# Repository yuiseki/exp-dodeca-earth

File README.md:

# exp-dodeca-earth

正十二面体の地球儀。12 の面それぞれに 1.28 インチの丸型 LCD (Waveshare 1.28inch LCD Module、GC9A01) を置き、その面から見た地球を映す。正十二面体は、面 6 枚ずつの同じお椀 2 個に分けて 3D プリントし、磁石で合わせる。お椀 1 個ぶんの LCD 6 枚を、XIAO ESP32-S3 1 枚と 74HC138 で駆動する。

## 中身

- `3d/pentagon/`: お椀と面の板の形 (版ごと)。`build.py` が STEP と STL を書く。いまの版は `v0.0.5` (同じお椀を 2 個印刷する)
- `simulate/`: 板と LCD を組み上げたときの当たり、磁石の極、ケーブルの取り回しを確かめるスクリプト
- `hardware/hub6_one/`: お椀 1 個ぶんの LCD 6 枚を駆動する基板 (1 枚、2 層)。`fab6/` が JLCPCB に出したファイル
- `hardware/hub6/`: 同じ役目の基板の、使わなかった案
- `firmware/hub6_bench/`: ブレッドボードで 6 枚を駆動するスケッチと、地球の画像を面ごとに切り出すスクリプト

## LCD モジュールの 3D 図面

`simulate/` のスクリプトは、Waveshare が配っている LCD モジュールの 3D 図面を読む。再配布の条件が書かれていないので、このリポジトリには入れていない。[Waveshare の wiki](https://www.waveshare.com/wiki/1.28inch_LCD_Module) の 3D Drawing (`1.28inch_LCD_Module_3D_Drawing.zip`) を取ってきて、`3d/display/` に展開する:

```sh
mkdir -p 3d/display && cd 3d/display
curl -LO https://files.waveshare.com/upload/4/49/1.28inch_LCD_Module_3D_Drawing.zip
unzip 1.28inch_LCD_Module_3D_Drawing.zip -d 1.28inch_LCD_Module_3D_Drawing
```

`3d/display/1.28inch_LCD_Module_3D_Drawing/1.28inch LCD Module 3D Drawing/0508.stp` ができればよい。LCD を含むメッシュ (`simulate/*/overlay.stl`、`overlay.3mf`、`dodecahedron*.3mf`) も同じ理由で入れていない。スクリプトを動かすと作られる。

## ライセンス

MIT (`LICENSE`)。

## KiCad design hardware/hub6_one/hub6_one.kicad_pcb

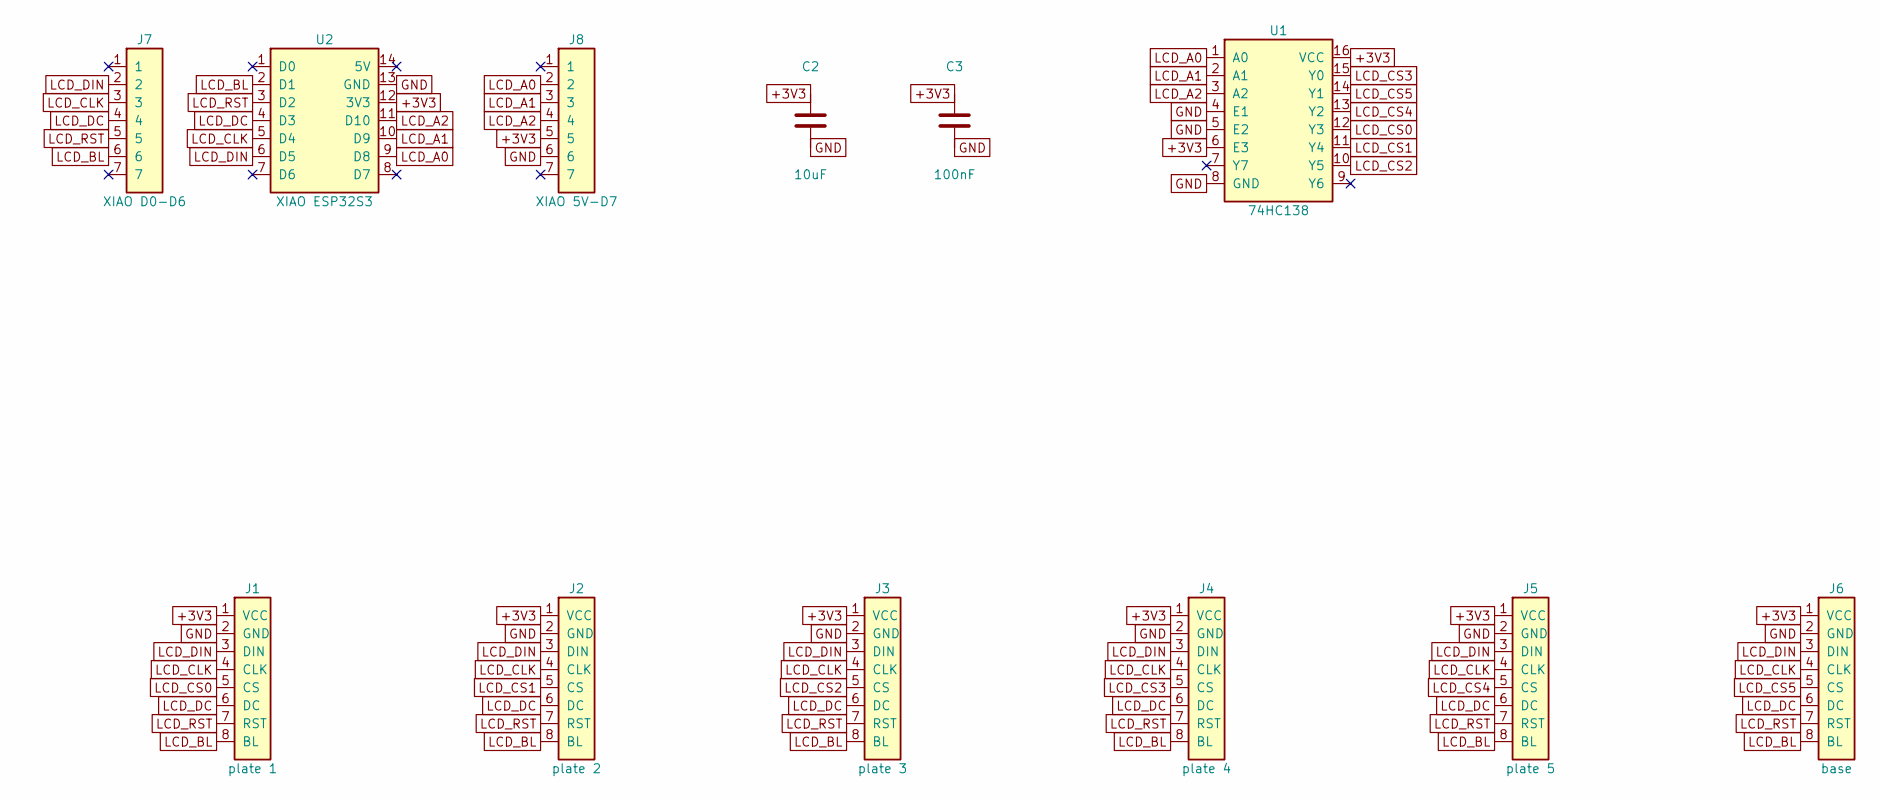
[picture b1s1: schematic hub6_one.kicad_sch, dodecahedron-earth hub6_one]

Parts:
C2: 10uF; C_0805_2012Metric; LCSC C15850
C3: 100nF; C_0603_1608Metric; LCSC C14663
J1: plate 1; Wire_1x08_P2.80
J2: plate 2; Wire_1x08_P2.80
J3: plate 3; Wire_1x08_P2.80
J4: plate 4; Wire_1x08_P2.80
J5: plate 5; Wire_1x08_P2.80
J6: base; Wire_2x04_P2.54
J7: XIAO D0-D6; PinSocket_1x07_P2.54mm_Vertical; LCSC C27985232
J8: XIAO 5V-D7; PinSocket_1x07_P2.54mm_Vertical; LCSC C27985232
U1: 74HC138; SOIC-16_3.9x9.9mm_P1.27mm; LCSC C2674688
U2: XIAO ESP32S3

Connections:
+3V3: C2.1, C3.1, J1.1 (VCC), J2.1 (VCC), J3.1 (VCC), J4.1 (VCC), J5.1 (VCC), J6.1 (VCC), J8.5, U1.6 (E3), U1.16 (VCC), U2.12 (3V3)
GND: C2.2, C3.2, J1.2 (GND), J2.2 (GND), J3.2 (GND), J4.2 (GND), J5.2 (GND), J6.2 (GND), J8.6, U1.4 (E1), U1.5 (E2), U1.8 (GND), U2.13 (GND)
LCD_A0: J8.2, U1.1 (A0), U2.9 (D8)
LCD_A1: J8.3, U1.2 (A1), U2.10 (D9)
LCD_A2: J8.4, U1.3 (A2), U2.11 (D10)
LCD_BL: J1.8 (BL), J2.8 (BL), J3.8 (BL), J4.8 (BL), J5.8 (BL), J6.8 (BL), J7.6, U2.2 (D1)
LCD_CLK: J1.4 (CLK), J2.4 (CLK), J3.4 (CLK), J4.4 (CLK), J5.4 (CLK), J6.4 (CLK), J7.3, U2.5 (D4)
LCD_CS0: J1.5 (CS), U1.12 (Y3)
LCD_CS1: J2.5 (CS), U1.11 (Y4)
LCD_CS2: J3.5 (CS), U1.10 (Y5)
LCD_CS3: J4.5 (CS), U1.15 (Y0)
LCD_CS4: J5.5 (CS), U1.13 (Y2)
LCD_CS5: J6.5 (CS), U1.14 (Y1)
LCD_DC: J1.6 (DC), J2.6 (DC), J3.6 (DC), J4.6 (DC), J5.6 (DC), J6.6 (DC), J7.4, U2.4 (D3)
LCD_DIN: J1.3 (DIN), J2.3 (DIN), J3.3 (DIN), J4.3 (DIN), J5.3 (DIN), J6.3 (DIN), J7.2, U2.6 (D5)
LCD_RST: J1.7 (RST), J2.7 (RST), J3.7 (RST), J4.7 (RST), J5.7 (RST), J6.7 (RST), J7.5, U2.3 (D2)

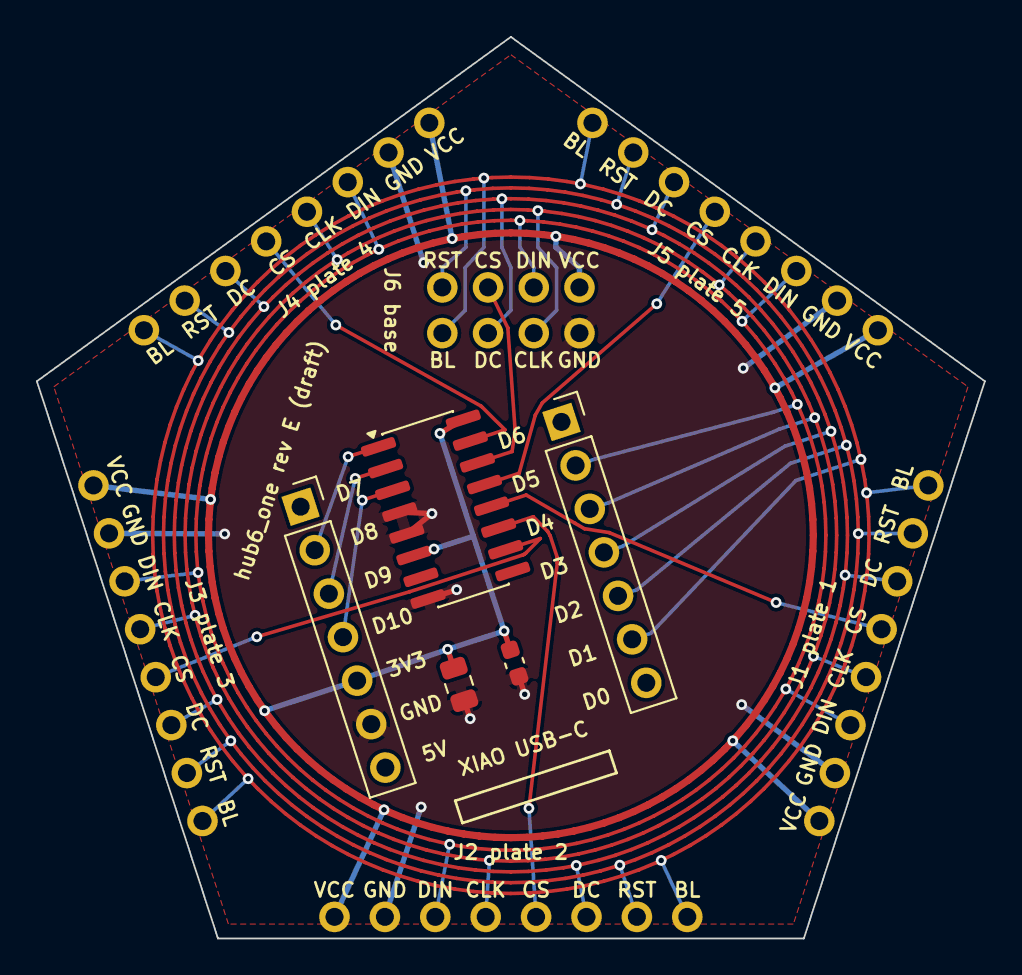
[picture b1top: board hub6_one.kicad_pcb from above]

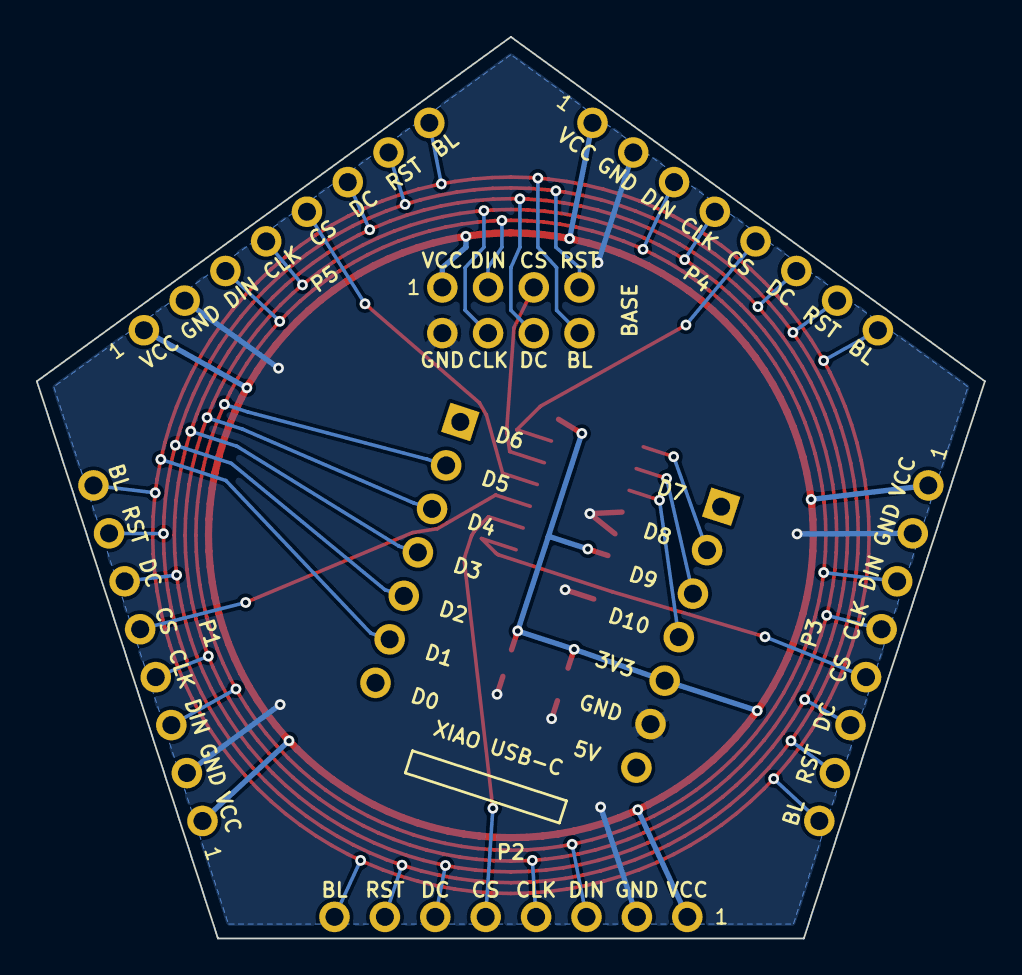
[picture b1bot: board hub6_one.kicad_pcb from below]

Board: 2 copper layers, 52.7 x 50.1 mm, 12 parts (7 on the bottom side), 16 nets.

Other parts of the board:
X1: XIAO; XIAO_ESP32S3_Hanging

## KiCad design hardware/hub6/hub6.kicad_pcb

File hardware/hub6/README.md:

# hub6

お椀 1 個ぶん、1.28 インチ丸型 LCD (Waveshare 1.28inch LCD Module、GC9A01、PH2.0 8 ピン) 6 枚を、XIAO ESP32-S3 1 枚と 74HC138 で駆動する基板。2 つのお椀に 1 枚ずつ載せる。

- 形: 辺までの距離 26 mm の正五角形。5 つの辺が、お椀の 5 枚の側面に 1 対 1 で向き合う。4 層、片面実装
- お椀の中の高さ: 基板の底面を、お椀の底の外面から 17〜20 mm に置くと、壁と当たらない (`3d/pentagon/v0.0.5/lcd_cup.stl` を輪切りにして測った。20 mm なら、壁との隙間 1 mm を取っても辺まで 27.4 mm まで入る)。固定の仕方は未定
- ケーブル: ディスプレイ側は PH2.0 のプラグ、基板側はより線 (26 AWG) のケーブル (Amazon B0GFCDKFH9、15 cm) を、現物合わせの長さに切って、基板の穴に直接はんだ付けする。ディスプレイ側は抜き差しできるので、基板を差し替えるときは、ケーブルごと取り替える
- J1〜J5: 側面のディスプレイ用の穴の列 (8 個、2.54 mm おき、穴 1.0 mm)。五角形の辺に沿って並び、ケーブルは上 (お椀の口の側) から来る。列の外側に、ケーブルを押さえる結束バンド (幅 2.5 mm) 用のスロットが 2 つずつある。ホットボンドで固めてもよい
- J6: 底面のディスプレイ用の穴の列。XIAO の右のソケット列のすぐ外側 (2.88 mm) にあり、底面のディスプレイのプラグのほぼ真上 (約 4 mm ずれ) にある。ケーブルは下から来るので、下から穴に通して、上面ではんだ付けする
- J7、J8: XIAO 用の 1x7、2.54 mm のメスのピンソケット (XFCN PM254V-11-07-H85、LCSC C2832270、高さ 8.5 mm)。XIAO は基板の中心に挿す (手で)。USB-C は方位 72 度を向く
- U1: 74HC138 (SOIC-16、LCSC C5602)。XIAO の下の、ソケットの 2 列の間に置く。A0、A1、A2 の 3 本から、6 枚の CS を作る。E1、E2 は GND、E3 は 3V3 に固定 (常に有効)
- C2: 10uF (LCSC C15850)、3.3V のバルク。C3: 100nF (LCSC C14663)、U1 の 3.3V。どちらも XIAO の下

## どの列がどのディスプレイか

お椀を底面で立てて、上から見て反時計回りに板 1〜5 (`simulate/v0.0.5/magnets.csv` と同じ番号)、そして底面。基板は、お椀の軸に中心を合わせ、方位 (上から見て反時計回り、お椀の座標と同じ) をそろえて置く。

| 列 | ディスプレイ | 基板上の方位 | CS のネット | U1 の出力 | アドレス (A2 A1 A0) |
|---|---|---|---|---|---|
| J1 | 板 1 | 198 度 | LCD_CS0 | Y0 (15 番) | 0 (000) |
| J2 | 板 2 | 270 度 | LCD_CS1 | Y1 (14 番) | 1 (001) |
| J3 | 板 3 | 342 度 | LCD_CS2 | Y2 (13 番) | 2 (010) |
| J4 | 板 4 | 54 度 | LCD_CS3 | Y3 (12 番) | 3 (011) |
| J5 | 板 5 | 126 度 | LCD_CS4 | Y5 (10 番) | 5 (101) |
| J6 | 底面 | XIAO の右 (162 度の側) | LCD_CS5 | Y4 (11 番) | 4 (100) |

アドレスの 6 と 7 (Y6、Y7) は使わない。ファームウェアでは、全部の CS を「選んでいない」状態にしたいときはアドレスを 7 にする (Y7 は何にもつながっていない)。

穴の番号は、ディスプレイの PH2.0 の番号と同じ: 1 VCC、2 GND、3 DIN、4 CLK、5 CS、6 DC、7 RST、8 BL (Waveshare の配線表の順。ピン番号の並びは、実機で確かめる)。ケーブルの線 n を、穴 n に入れる。1 番の穴は、シルクの「1」の側。側面の列 (J1〜J5) では、上から見て反時計回りの端。

共有の信号 (6 枚とも同じ) と、XIAO のピン:

| 信号 | XIAO のピン |
|---|---|
| LCD_DIN (SPI MOSI) | D0 |
| LCD_CLK (SPI SCK) | D1 |
| LCD_DC | D3 |
| LCD_RST | D4 |
| LCD_BL | D5 |
| A0、A1、A2 (74HC138 のアドレス) | D7、D8、D9 |
| つないでいない (予備) | D2、D6、D10 |

この並びは、J6 の穴 3、4、6、7、8 が、XIAO の D0、D1、D3、D4、D5 の真横に来るように決めた (D2 の横は J6 の 5 番、CS)。SPI は GPIO マトリクス経由なので、どのピンでも動く。D2 (GPIO3) はストラッピングピン、D6/D7 (GPIO43/44) は UART0。D2、D6、D10 の 3 本が空いているので、2 台の同期は、配線 (予備の 1 本) か、ESP-NOW などの無線のどちらでも取れる。

74HC138 は 3.3V で動かす (HC 系は 2V から 6V)。出力の「高」は電源に近い電圧なので、ディスプレイ側の TXB0108 のしきい値 (3.3V のとき 2.15V) を超える。出力が切り替わる瞬間に、短いひげ (グリッチ) が CS に出ることがあるが、SCK が止まっている間なので、ディスプレイは何も読み込まない。ただし、アドレスは SCK が止まっているとき (転送の合間) にだけ変えること。

## 電源は 3.3V

ディスプレイの VCC は XIAO の 3V3 に直結し、XIAO の 5V ピンは使わない。理由: ディスプレイは 5V→3.3V の電源 IC と、TXB0108 のレベル変換 IC を載せていて、その信号側の基準電圧は VCC。VCC を 5V にすると、信号の「高」の下限は 0.65 x 5V = 3.25V (TXB0108 のデータシート 5.3) で、XIAO の 3.3V の出力 (ESP32-S3 は下限 2.64V) では読み取りが保証されない。VCC = 3.3V なら下限は 2.15V。

6 枚で約 190 mA (74HC138 は数 uA で、足しても変わらない) (Waveshare の最大値、1 枚 31.2 mA)。XIAO の 3V3 ピンは 700 mA (Seeed の記載) まで取れる。USB 給電の間は、XIAO のレギュレーターが (5 - 3.3)V x 約 0.3A = 約 0.5W の熱を出す。実機で温度を測る。

## 層

| 層 | 中身 |
|---|---|
| F.Cu | 信号の短い線 (各列から輪への放射状の線、XIAO から J6 と U1 への線、U1 の出力から via への線、via から側面の列の 5 番までの線)、部品 |
| In1.Cu | GND の面 |
| In2.Cu | 共有の 5 信号の輪 (中心を囲む同心円。半径 17.6、18.4、19.2、20.0、20.8 mm。どの信号がどの輪かは `layout.json`)。輪の内側 (半径 17.1 mm まで) は、U1 の 6 本の出力の線 (CS) が、ソケットのピンの隙間を縫って走る |
| B.Cu | +3V3 の面 |

スルーホールのパッドは、GND と +3V3 の面に直接つながる。側面の列は内向きに、J6 は外向きに、放射状の線で輪につながる。XIAO は J6 を通して輪につながる。配線は自動配線ではなく、`assign.py` が探して `layout.json` に書いた線を `make.py` が引く (Freerouting は 2 層でも 4 層でも、共有バスと選択線の構造を見つけられずに止まった)。

## 作り方

```sh
/usr/bin/python3 make.py    # 回路図、部品と配線を置いた基板、ライブラリ (KiCad 10 の pcbnew モジュールを使う)
./check.sh                  # ERC、DRC (回路図との突き合わせ込み)、test_hub6.py。どれも 0 件で通る
/usr/bin/python3 fab.py     # JLCPCB 用: build/fab/ にガーバーとドリルの zip、BOM、部品配置 (CPL)。fab6/ に写す
../../.venv/bin/python assign.py   # 配線を探し直して layout.json を書く (shapely が要る。数秒)
```

- 部品と網の表は `make.py` の先頭にあり、回路図と基板の両方がそこから作られる
- `test_hub6.py` は `make.py` とは別に、設計表から各パッドの網と、列の位置と向き、XIAO と部品の位置、穴とスロットの大きさを確かめる
- `assign.py`: ① 共有 5 信号を、どの輪に載せるか (J6 と側面の列からの放射状の線が、互いにぶつからない順を探す。120 通りのうち 4 通りが通る)。② 74HC138 の出力 6 本を、どの列につなぎ、どこで In2 から F.Cu に上げ、In2 のどこを通すか (ソケットの隙間を通る最短経路を、見通しグラフで探す)。結果が `layout.json` で、`make.py` と `test_hub6.py` はこの結果を前提にする (テストの表は手で写してあるので、`layout.json` を変えたらテストも直す)

## JLCPCB での組み立て

- 経済的な実装 (Economic PCBA) は、4 層に対応し、片面 (上面) だけ。載せる部品はすべて上面
- 載せる部品は U1、C2、C3 (表面実装) と、J7、J8 (XIAO のソケット、スルーホールの手はんだ、Manual Assembly、1 か所 0.0164 ドル)。J1〜J6 は穴だけで、部品はない (BOM と CPL に出ない)
- U1 (C5602) は、JLCPCB の拡張部品 (Extended)。基本部品ではないので、部品の種類ごとに追加費用が 1 種類ぶんかかる。C2 (C15850) と C3 (C14663) は基本部品
- 五角形の外形と、側面の列のスロット (1.3 x 2.9 mm の長穴、メッキなし) は、見積もりの画面で通るか確かめる

## 発注の前に確かめること

- XIAO で 6 枚を実際に駆動して、画面の乱れ、更新の速さ (40MHz で 6 枚を順に送ると約 7fps)、XIAO のレギュレーターの温度を確かめる (実機でしか分からない)
- JLCPCB の部品配置の確認画面で、U1 と J7、J8 の向き。SOIC-16 とソケットの JLCPCB 上の向きは、cubic-earth の hub3 で確かめた補正 (`fab.py` の `JLC_ROTATION_OFFSET`) を使っているが、この基板では未確認
- 4 層の基板の費用
- ケーブルの 1 番の線の色。ディスプレイ側のヘッダーの 1 番 (VCC) が、ケーブルのどの色の線になるかを、テスターで確かめてから穴に入れる
- 底面のディスプレイのプラグの 1 番が、J6 の 1 番 (XIAO の USB-C の側) と同じ向きか。逆なら、線が 8 本とも J6 の上で交差する (動きはするが、はんだ付けの間違いが起きやすい)

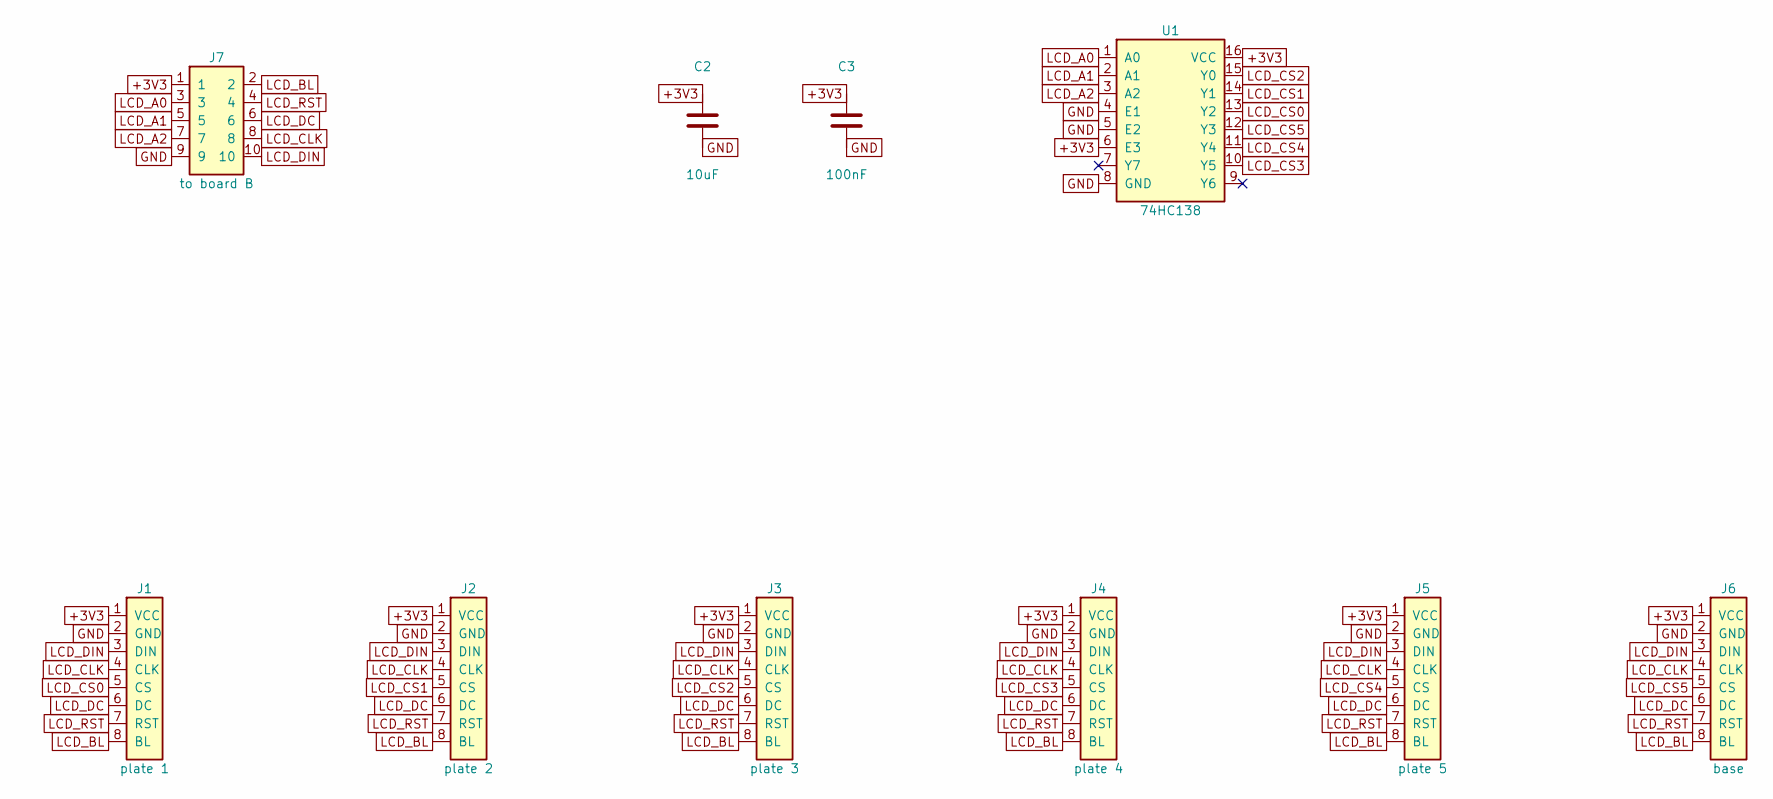
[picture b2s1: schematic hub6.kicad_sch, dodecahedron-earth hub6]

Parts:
C2: 10uF; C_0805_2012Metric; LCSC C15850
C3: 100nF; C_0603_1608Metric; LCSC C14663
J1: plate 1; Wire_1x08_P2.54_Tie
J2: plate 2; Wire_1x08_P2.54_Tie
J3: plate 3; Wire_1x08_P2.54_Tie
J4: plate 4; Wire_1x08_P2.54_Tie
J5: plate 5; Wire_1x08_P2.54_Tie
J6: base; Wire_2x04_P2.54
J7: to board B; PinHeader_2x05_P2.54mm_Vertical
U1: 74HC138; SOIC-16_3.9x9.9mm_P1.27mm; LCSC C5602

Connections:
+3V3: C2.1, C3.1, J1.1 (VCC), J2.1 (VCC), J3.1 (VCC), J4.1 (VCC), J5.1 (VCC), J6.1 (VCC), J7.1, U1.6 (E3), U1.16 (VCC)
GND: C2.2, C3.2, J1.2 (GND), J2.2 (GND), J3.2 (GND), J4.2 (GND), J5.2 (GND), J6.2 (GND), J7.9, U1.4 (E1), U1.5 (E2), U1.8 (GND)
LCD_A0: J7.3, U1.1 (A0)
LCD_A1: J7.5, U1.2 (A1)
LCD_A2: J7.7, U1.3 (A2)
LCD_BL: J1.8 (BL), J2.8 (BL), J3.8 (BL), J4.8 (BL), J5.8 (BL), J6.8 (BL), J7.2
LCD_CLK: J1.4 (CLK), J2.4 (CLK), J3.4 (CLK), J4.4 (CLK), J5.4 (CLK), J6.4 (CLK), J7.8
LCD_CS0: J1.5 (CS), U1.13 (Y2)
LCD_CS1: J2.5 (CS), U1.14 (Y1)
LCD_CS2: J3.5 (CS), U1.15 (Y0)
LCD_CS3: J4.5 (CS), U1.10 (Y5)
LCD_CS4: J5.5 (CS), U1.11 (Y4)
LCD_CS5: J6.5 (CS), U1.12 (Y3)
LCD_DC: J1.6 (DC), J2.6 (DC), J3.6 (DC), J4.6 (DC), J5.6 (DC), J6.6 (DC), J7.6
LCD_DIN: J1.3 (DIN), J2.3 (DIN), J3.3 (DIN), J4.3 (DIN), J5.3 (DIN), J6.3 (DIN), J7.10
LCD_RST: J1.7 (RST), J2.7 (RST), J3.7 (RST), J4.7 (RST), J5.7 (RST), J6.7 (RST), J7.4

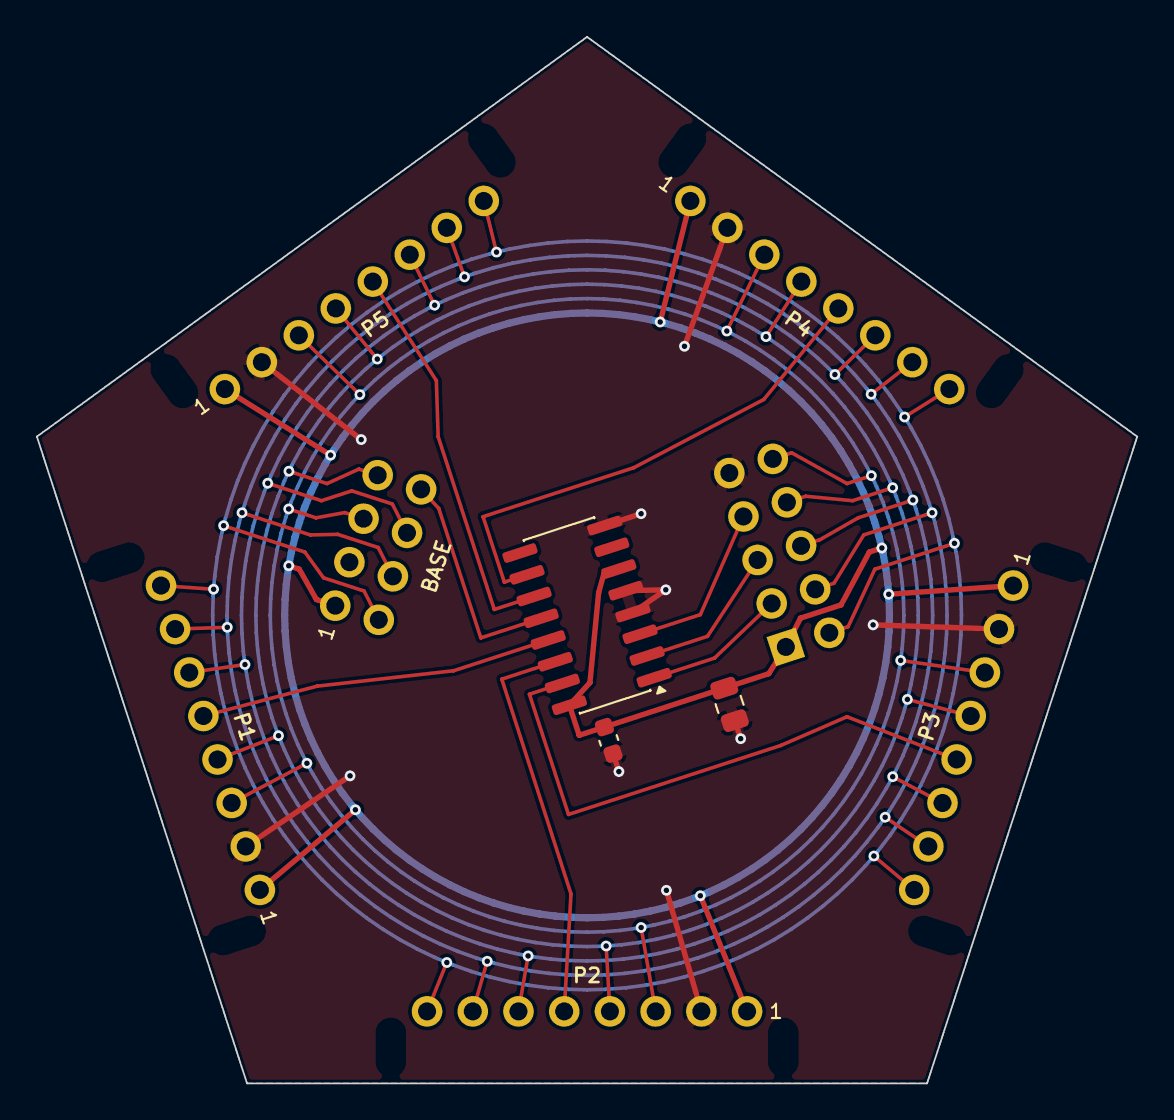
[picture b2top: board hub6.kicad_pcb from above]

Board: 2 copper layers, 61.1 x 58.1 mm, 10 parts (1 on the bottom side), 16 nets.

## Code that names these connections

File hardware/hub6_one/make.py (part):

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# from VCC, and at 5V it wants 0.65 x 5V = 3.25V for a high, which a 3.3V XIAO pin does not
# guarantee (ESP32-S3 VOH min 2.64V); at 3.3V it wants 2.15V.
PH_PINS = ["VCC", "GND", "DIN", "CLK", "CS", "DC", "RST", "BL"]
BUS_PIN = {"LCD_DIN": 3, "LCD_CLK": 4, "LCD_DC": 6, "LCD_RST": 7, "LCD_BL": 8}
# B.Cu rings, centre to the track's centre line. Nothing on B.Cu crosses them, so any order works.
RING = {"+3V3": 16.8, "LCD_DIN": 17.5, "LCD_CLK": 18.1, "LCD_DC": 18.7, "LCD_RST": 19.3, "LCD_BL": 19.9}  # rev D: 0.8 apart to 20.8; 0.55 apart breaks the 0.15 clearance at the vias
RING_W = {"+3V3": 0.4}
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    # pins 1..8 on U1's -x side, 9..16 on its +x side (the outputs face the XIAO's D0..D6 column), pin 1 at the +y end
    assert u1_xy(u1_pad(1))[0] < 0 < u1_xy(u1_pad(9))[0] and u1_xy(u1_pad(1))[1] > 0 > u1_xy(u1_pad(8))[1]
    # A0..A2: F.Cu from the XIAO pins to a via just beyond U1's pins 1..3; the order along y is the same at both ends
    a_pins = {"LCD_A0": 1, "LCD_A1": 2, "LCD_A2": 3}
    for a, name in XIAO_NETS.items():
        if name in a_pins:
            v = along(u1_pad(a_pins[name]), -1.775)
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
